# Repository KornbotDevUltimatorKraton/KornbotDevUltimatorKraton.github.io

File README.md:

# KornbotDevUltimatorKraton.github.io

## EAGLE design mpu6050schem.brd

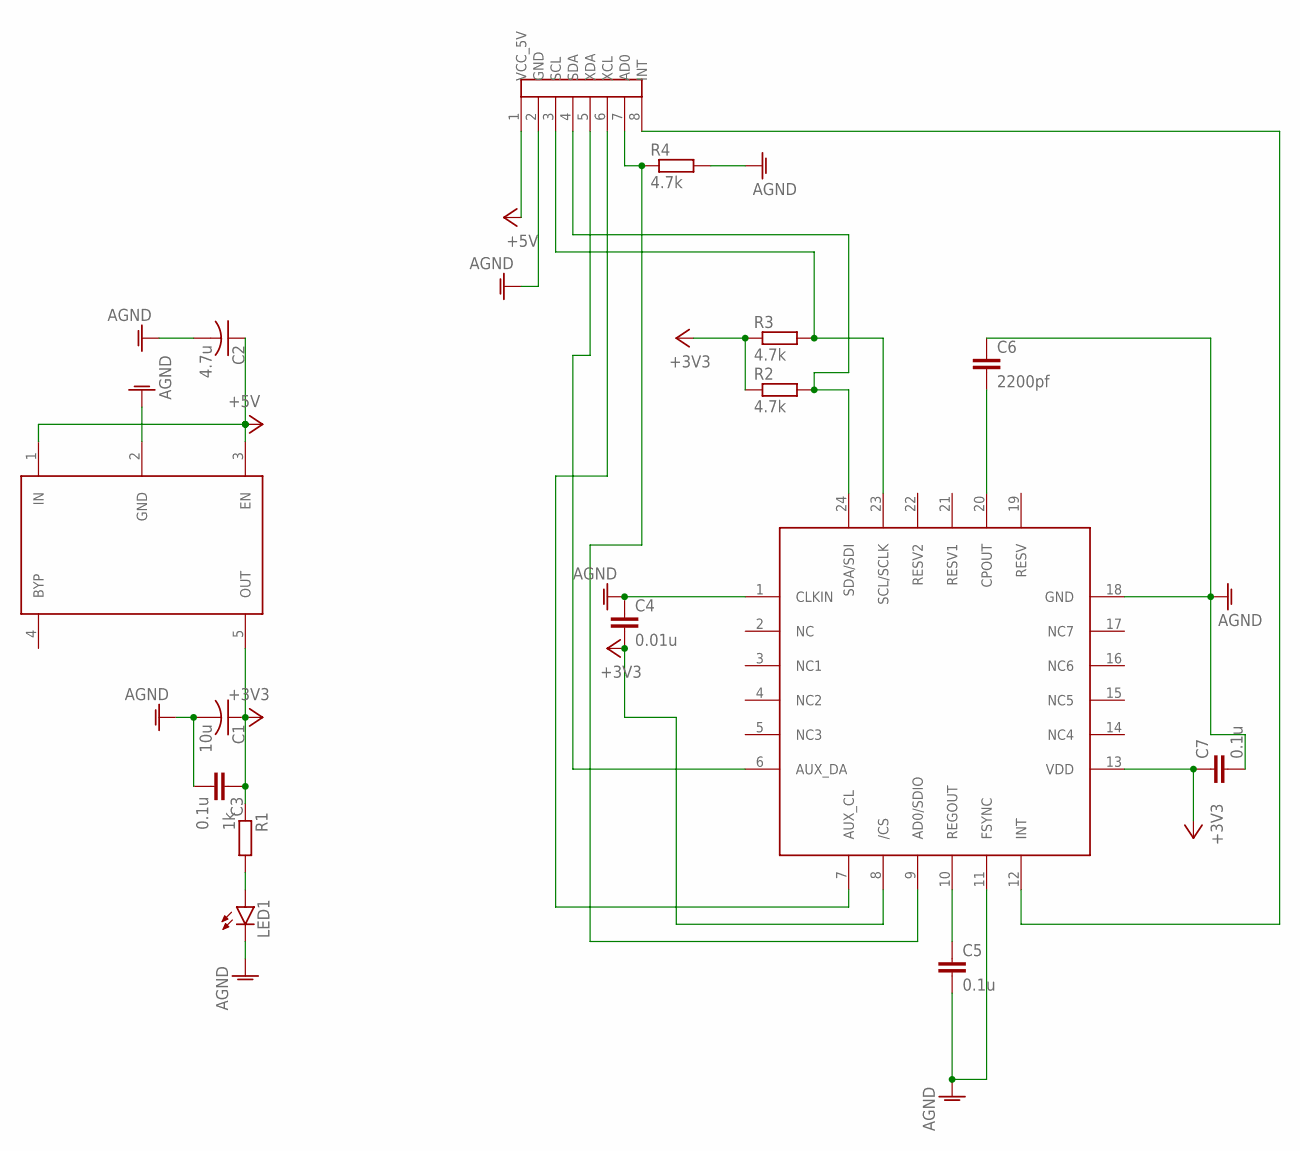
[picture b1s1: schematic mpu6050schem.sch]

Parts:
C1: 10u; C0603
C2: 4.7u; C0603
C3, C5, C7: 0.1u; C0402
C4: 0.01u; C0402
C6: 2200pf; C0402
LDO3.3V: MIC5219; SOT95P295X145-5N
LED1: LEDCHIP-LED0603; CHIP-LED0603
R1: 1k; R0402
R2, R3, R4: 4.7k; R0402
U$1: MPU6050; QFN50P395X395X90-25T265X255N
U$2: 8PINSHEADER; HDRRA8W64P254_1X8_2032X254X556B

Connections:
+3V3: C1.1, C3.1, C4.2, C7.1, LDO3.3V.5 (OUT), R1.1, R2.1, R3.1, U$1.8 (/CS), U$1.13 (VDD)
+5V: C2.1, LDO3.3V.1 (IN), LDO3.3V.3 (EN), U$2.1 (VCC_5V)
AGND: C1.2, C2.2, C3.2, C4.1, C5.2, C6.1, C7.2, LDO3.3V.2 (GND), LED1.C, R4.2, U$1.1 (CLKIN), U$1.11 (FSYNC), U$1.18 (GND), U$2.2 (GND)
unnamed: LED1.A, R1.2
unnamed: R2.2, U$1.24 (SDA/SDI), U$2.4 (SDA)
unnamed: R3.2, U$1.23 (SCL/SCLK), U$2.3 (SCL)
unnamed: C5.1, U$1.10 (REGOUT)
unnamed: C6.2, U$1.20 (CPOUT)
unnamed: R4.1, U$1.9 (AD0/SDIO), U$2.7 (AD0)
unnamed: U$1.12 (INT), U$2.8 (INT)
unnamed: U$1.6 (AUX_DA), U$2.5 (XDA)
unnamed: U$1.7 (AUX_CL), U$2.6 (XCL)

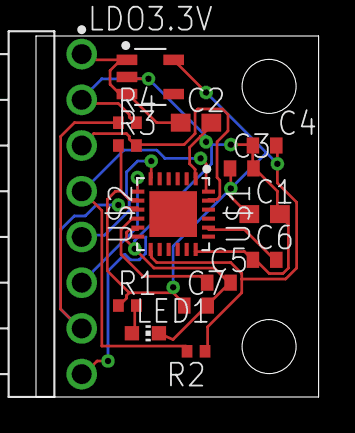
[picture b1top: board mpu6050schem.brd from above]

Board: 2 copper layers, 15.7 x 20.1 mm, 15 parts (0 on the bottom side), 12 nets.
